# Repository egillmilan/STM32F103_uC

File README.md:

# STM32F103_uC
 A control board for a reflow hot plate project. The microcontroller being used is the STM32F103C8T6.

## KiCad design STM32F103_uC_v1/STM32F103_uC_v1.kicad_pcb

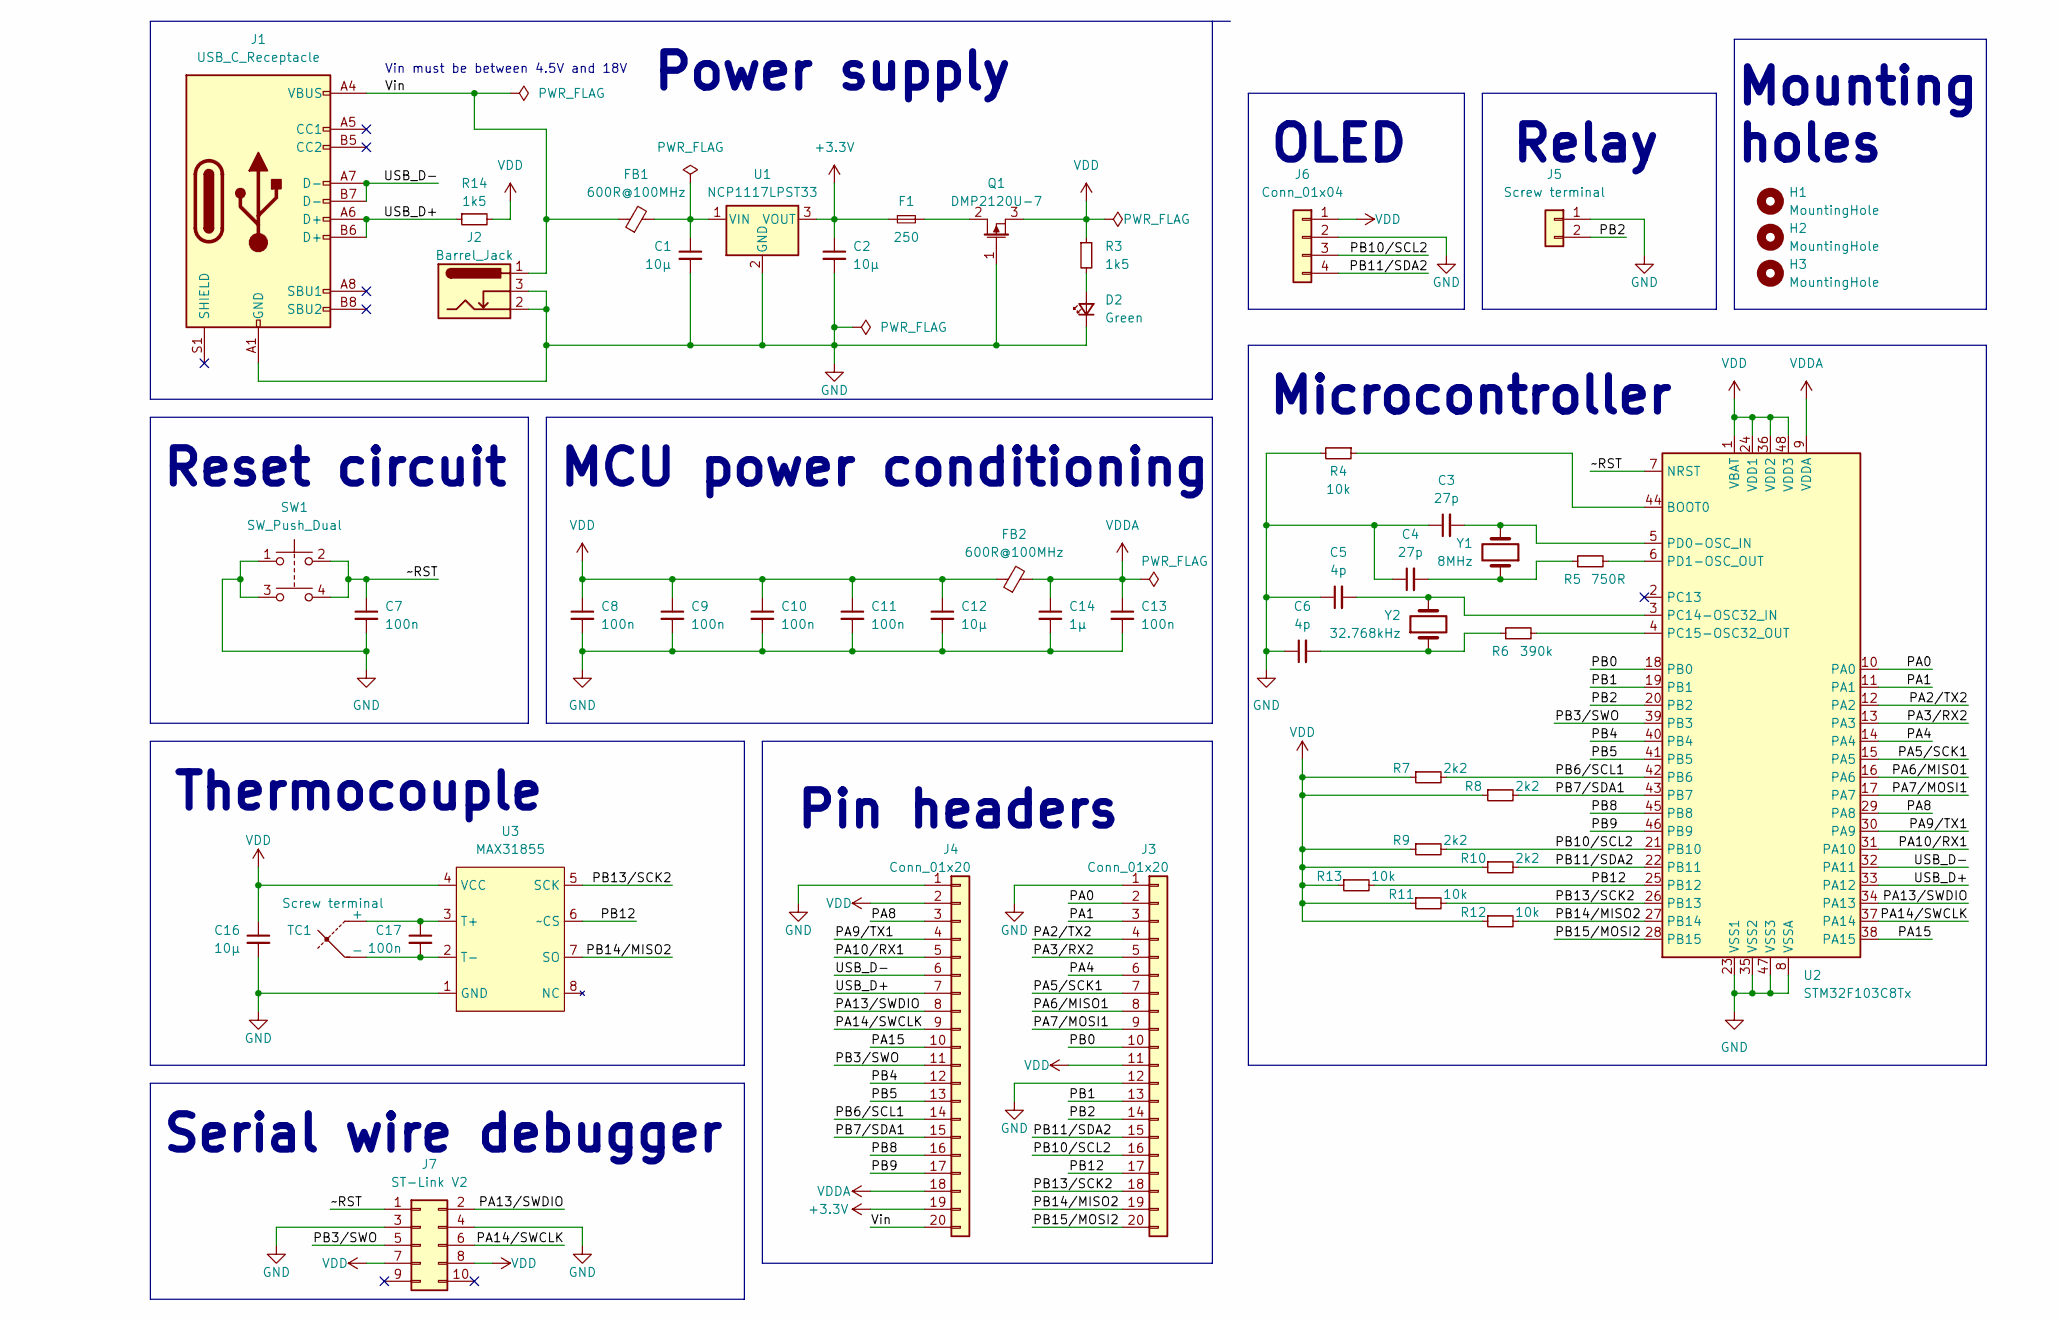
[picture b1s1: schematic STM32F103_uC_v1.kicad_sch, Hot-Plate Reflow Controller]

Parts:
C1, C2, C12, C16: 10µ; C_0805_2012Metric_Pad1.18x1.45mm_HandSolder
C3, C4: 27p; C_0805_2012Metric_Pad1.18x1.45mm_HandSolder
C5, C6: 4p; C_0805_2012Metric_Pad1.18x1.45mm_HandSolder
C7, C8, C9, C10, C11, C13, C17: 100n; C_0805_2012Metric_Pad1.18x1.45mm_HandSolder
C14: 1µ; C_0805_2012Metric_Pad1.18x1.45mm_HandSolder
D2: Green; LED_1206_3216Metric_Pad1.42x1.75mm_HandSolder
F1: 250; Fuse_1206_3216Metric_Pad1.42x1.75mm_HandSolder
FB1, FB2: 600R@100MHz; L_0805_2012Metric_Pad1.15x1.40mm_HandSolder
H1, H2, H3: MountingHole; MountingHole_3.2mm_M3
J1: USB_C_Receptacle; USB_C_Receptacle_GCT_USB4085
J2: Barrel_Jack; BarrelJack_Horizontal
J3, J4: Conn_01x20; PinHeader_1x20_P2.54mm_Vertical
J5: Screw terminal; TerminalBlock_Phoenix_MPT-0,5-2-2.54_1x02_P2.54mm_Horizontal
J6: Conn_01x04; 1.3_inch_OLED_IIC
J7: ST-Link V2; PinSocket_2x05_P2.54mm_Vertical
Q1: DMP2120U-7; SC-59_Handsoldering
R3, R14: 1k5; R_0805_2012Metric_Pad1.20x1.40mm_HandSolder
R4, R11, R12, R13: 10k; R_0805_2012Metric_Pad1.20x1.40mm_HandSolder
R5: 750R; R_0805_2012Metric_Pad1.20x1.40mm_HandSolder
R6: 390k; R_0805_2012Metric_Pad1.20x1.40mm_HandSolder
R7, R8, R9, R10: 2k2; R_0805_2012Metric_Pad1.20x1.40mm_HandSolder
SW1: SW_Push_Dual; SW_Push_1P1T_NO_CK_KSC6xxJ
TC1: Screw terminal; TerminalBlock_Phoenix_MPT-0,5-2-2.54_1x02_P2.54mm_Horizontal
U1: NCP1117LPST33; SOT-223-3_TabPin2
U2: STM32F103C8Tx; LQFP-48_7x7mm_P0.5mm
U3: MAX31855; SOIC-8_3.9x4.9mm_P1.27mm
Y1: 8MHz; Crystal_SMD_Abracon_ABM3-2Pin_5.0x3.2mm_HandSoldering
Y2: 32.768kHz; Crystal_SMD_MicroCrystal_CC7V-T1A-2Pin_3.2x1.5mm_HandSolder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

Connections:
+3V3: C2.1, F1.1, J4.19, U1.3 (VOUT)
/PA0: J3.2, U2.10 (PA0)
/PA1: J3.3, U2.11 (PA1)
/PA2/TX2: J3.4, U2.12 (PA2)
/PA3/RX2: J3.5, U2.13 (PA3)
/PA4: J3.6, U2.14 (PA4)
/PA5/SCK1: J3.7, U2.15 (PA5)
/PA6/MISO1: J3.8, U2.16 (PA6)
/PA7/MOSI1: J3.9, U2.17 (PA7)
/PA8: J4.3, U2.29 (PA8)
/PA9/TX1: J4.4, U2.30 (PA9)
/PA10/RX1: J4.5, U2.31 (PA10)
/PA13/SWDIO: J4.8, J7.2, U2.34 (PA13)
/PA14/SWCLK: J4.9, J7.6, U2.37 (PA14)
/PA15: J4.10, U2.38 (PA15)
/PB0: J3.10, U2.18 (PB0)
/PB1: J3.13, U2.19 (PB1)
/PB2: J3.14, J5.2, U2.20 (PB2)
/PB3/SWO: J4.11, J7.5, U2.39 (PB3)
/PB4: J4.12, U2.40 (PB4)
/PB5: J4.13, U2.41 (PB5)
/PB6/SCL1: J4.14, R7.2, U2.42 (PB6)
/PB7/SDA1: J4.15, R8.2, U2.43 (PB7)
/PB8: J4.16, U2.45 (PB8)
/PB9: J4.17, U2.46 (PB9)
/PB10/SCL2: J3.16, J6.3, R9.2, U2.21 (PB10)
/PB11/SDA2: J3.15, J6.4, R10.2, U2.22 (PB11)
/PB12: J3.17, R13.2, U2.25 (PB12), U3.6 (~CS)
/PB13/SCK2: J3.18, R11.2, U2.26 (PB13), U3.5 (SCK)
/PB14/MISO2: J3.19, R12.2, U2.27 (PB14), U3.7 (SO)
/PB15/MOSI2: J3.20, U2.28 (PB15)
/USB_D+: J1.A6 (D+), J1.B6 (D+), J4.7, R14.1, U2.33 (PA12)
/USB_D-: J1.A7 (D-), J1.B7 (D-), J4.6, U2.32 (PA11)
/Vin: FB1.1, J1.A4 (VBUS), J1.A9 (VBUS), J1.B4 (VBUS), J1.B9 (VBUS), J2.1, J4.20
/~RST: C7.1, J7.1, SW1.2, SW1.4, U2.7 (NRST)
GND: C1.2, C2.2, C3.1, C4.1, C5.1, C6.1, C7.2, C8.2, C9.2, C10.2, C11.2, C12.2, C13.2, C14.2, C16.2, D2.1 (K), J1.A1 (GND), J1.A12 (GND), J1.B1 (GND), J1.B12 (GND), J2.2, J2.3, J3.1, J3.12, J4.1, J5.1, J6.2, J7.3, J7.4, Q1.1, R4.2, SW1.1, SW1.3, U1.2 (GND), U2.8 (VSSA), U2.23 (VSS1), U2.35 (VSS2), U2.47 (VSS3), U3.1 (GND)
unnamed: C1.1, FB1.2, U1.1 (VIN)
unnamed: C3.2, U2.5 (PD0-OSC_IN), Y1.2
unnamed: C4.2, R5.1, Y1.1
unnamed: C5.2, U2.3 (PC14-OSC32_IN), Y2.2
unnamed: C6.2, R6.1, Y2.1
unnamed: C17.1, TC1.1 (+), U3.3 (T+)
unnamed: C17.2, TC1.2 (-), U3.2 (T-)
unnamed: D2.2 (A), R3.2
unnamed: F1.2, Q1.2
unnamed: R4.1, U2.44 (BOOT0)
unnamed: R5.2, U2.6 (PD1-OSC_OUT)
unnamed: R6.2, U2.4 (PC15-OSC32_OUT)
VDD: C8.1, C9.1, C10.1, C11.1, C12.1, C16.1, FB2.1, J3.11, J4.2, J6.1, J7.7, J7.8, Q1.3, R3.1, R7.1, R8.1, R9.1, R10.1, R11.1, R12.1, R13.1, R14.2, U2.1 (VBAT), U2.24 (VDD1), U2.36 (VDD2), U2.48 (VDD3), U3.4 (VCC)
VDDA: C13.1, C14.1, FB2.2, J4.18, U2.9 (VDDA)

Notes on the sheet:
Pin headers
Reset circuit
MCU power conditioning
Vin must be between 4.5V and 18V
OLED
Power supply
Microcontroller
Relay
Serial wire debugger
Thermocouple
Mounting holes

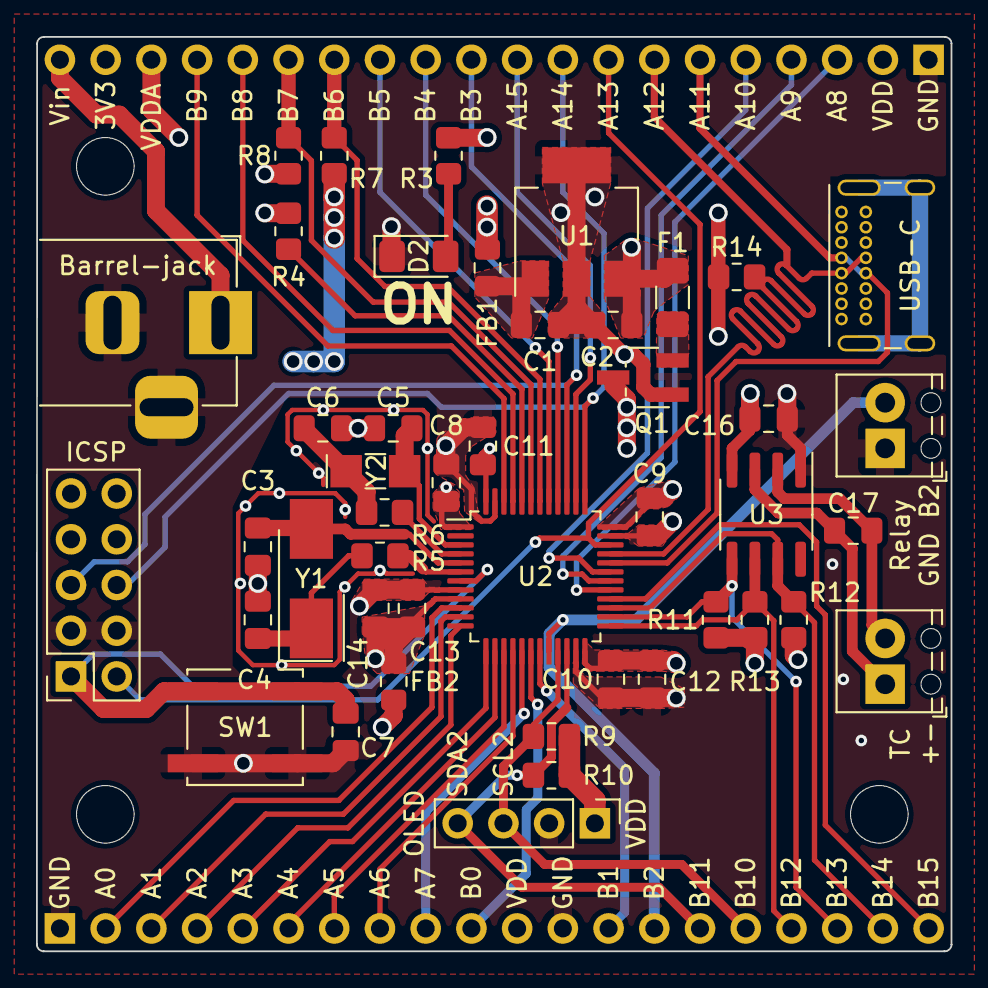
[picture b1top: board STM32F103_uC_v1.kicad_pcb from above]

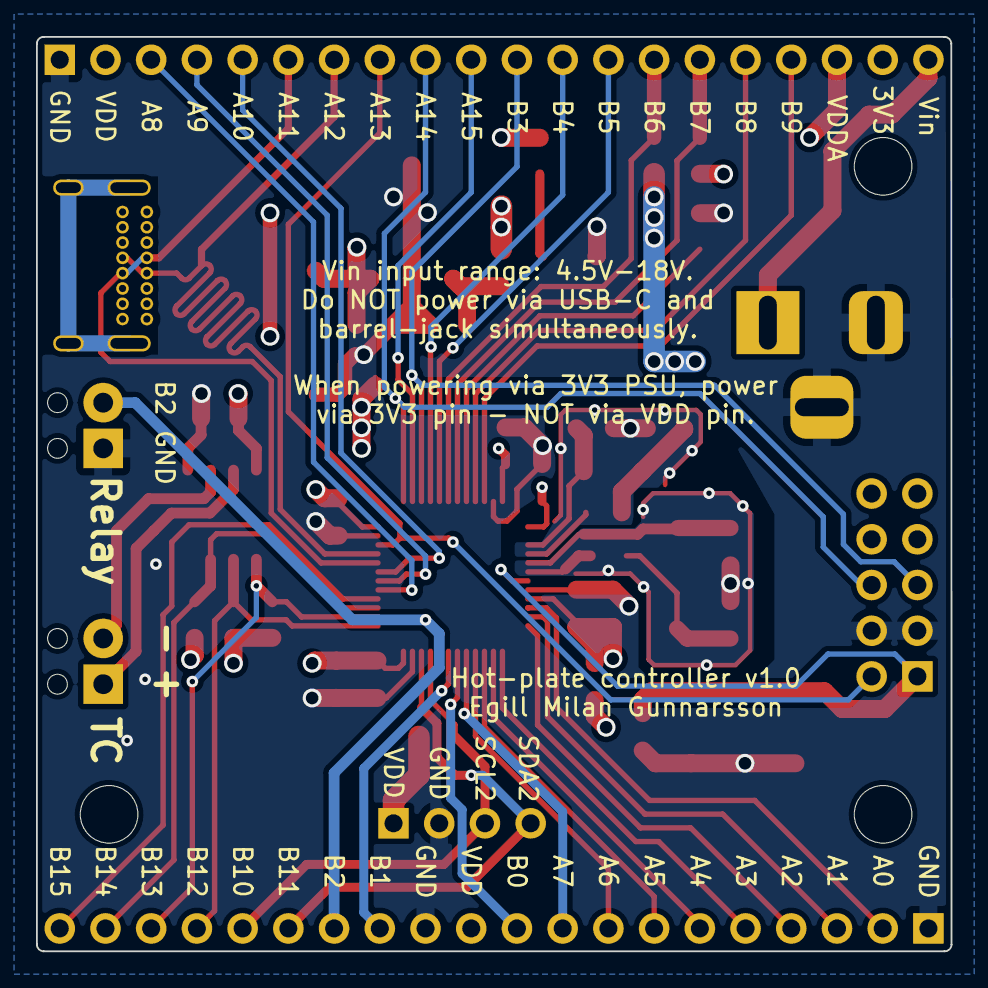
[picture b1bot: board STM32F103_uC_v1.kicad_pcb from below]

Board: 4 copper layers, 50.8 x 50.8 mm, 50 parts (2 on the bottom side), 50 nets.

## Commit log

2022-04-07 100nF -> 10nF
2022-04-08 Added datasheets
2022-04-08 maintenacne
2022-04-11 Schematic additions
2022-04-12 Small schematic changes
2022-04-12 cleanup
2022-05-09 Version 1.0
2022-05-20 Finishing touches
2022-05-20 Added Gerbers
2022-08-24 Fixed LDO pinout
2023-03-23 added images
